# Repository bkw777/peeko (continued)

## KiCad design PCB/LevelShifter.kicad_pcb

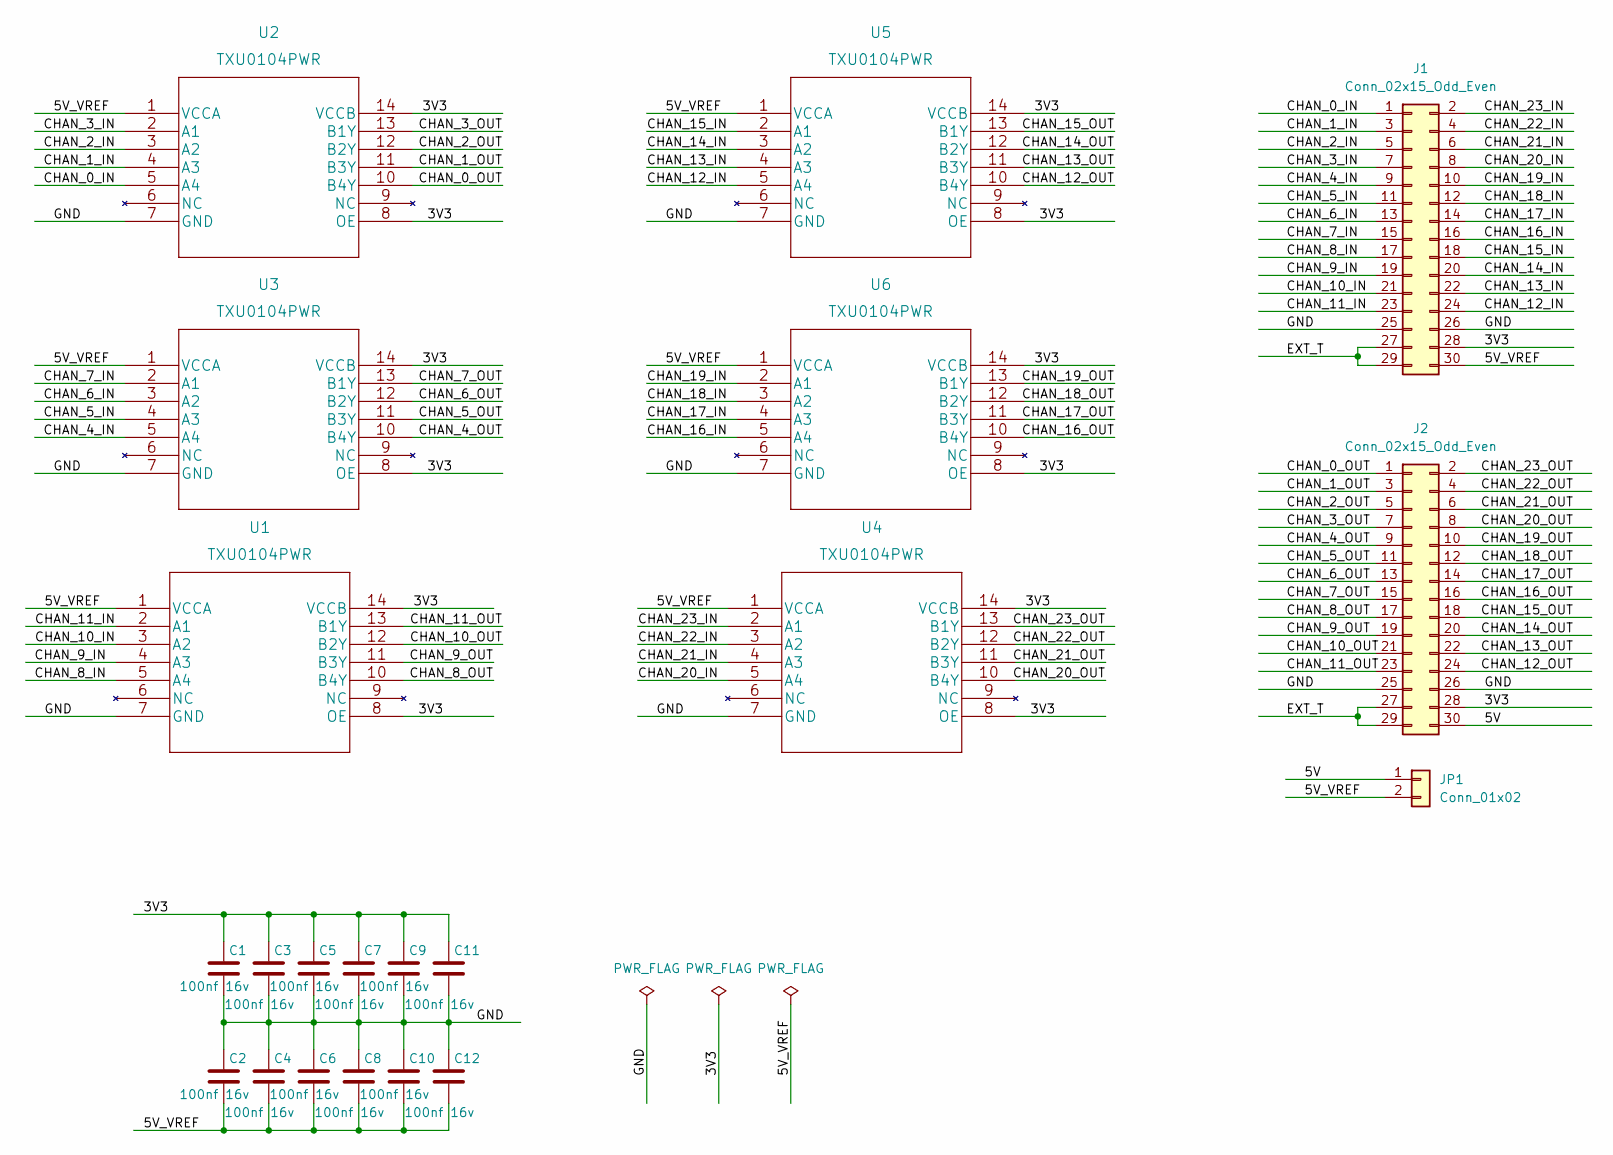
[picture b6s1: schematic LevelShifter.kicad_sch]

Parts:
C1, C2, C3, C4, C5, C6, C7, C8, C9, C10, C11, C12: 100nf 16v; C_0603_1608Metric
J1: Conn_02x15_Odd_Even; PinSocket_2x15_P2.54mm_Horizontal
J2: Conn_02x15_Odd_Even; PinHeader_2x15_P2.54mm_Horizontal
JP1: Conn_01x02; PinHeader_1x02_P2.54mm_Vertical
U1, U2, U3, U4, U5, U6: TXU0104PWR

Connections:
/3V3: C1.1, C3.1, C5.1, C7.1, C9.1, C11.1, J1.28, J2.28, U1.8 (OE), U1.14 (VCCB), U2.8 (OE), U2.14 (VCCB), U3.8 (OE), U3.14 (VCCB), U4.8 (OE), U4.14 (VCCB), U5.8 (OE), U5.14 (VCCB), U6.8 (OE), U6.14 (VCCB)
/5V: J2.30, JP1.1
/5V_VREF: C2.2, C4.2, C6.2, C8.2, C10.2, C12.2, J1.30, JP1.2, U1.1 (VCCA), U2.1 (VCCA), U3.1 (VCCA), U4.1 (VCCA), U5.1 (VCCA), U6.1 (VCCA)
/CHAN_0_IN: J1.1, U2.5 (A4)
/CHAN_0_OUT: J2.1, U2.10 (B4Y)
/CHAN_1_IN: J1.3, U2.4 (A3)
/CHAN_1_OUT: J2.3, U2.11 (B3Y)
/CHAN_2_IN: J1.5, U2.3 (A2)
/CHAN_2_OUT: J2.5, U2.12 (B2Y)
/CHAN_3_IN: J1.7, U2.2 (A1)
/CHAN_3_OUT: J2.7, U2.13 (B1Y)
/CHAN_4_IN: J1.9, U3.5 (A4)
/CHAN_4_OUT: J2.9, U3.10 (B4Y)
/CHAN_5_IN: J1.11, U3.4 (A3)
/CHAN_5_OUT: J2.11, U3.11 (B3Y)
/CHAN_6_IN: J1.13, U3.3 (A2)
/CHAN_6_OUT: J2.13, U3.12 (B2Y)
/CHAN_7_IN: J1.15, U3.2 (A1)
/CHAN_7_OUT: J2.15, U3.13 (B1Y)
/CHAN_8_IN: J1.17, U1.5 (A4)
/CHAN_8_OUT: J2.17, U1.10 (B4Y)
/CHAN_9_IN: J1.19, U1.4 (A3)
/CHAN_9_OUT: J2.19, U1.11 (B3Y)
/CHAN_10_IN: J1.21, U1.3 (A2)
/CHAN_10_OUT: J2.21, U1.12 (B2Y)
/CHAN_11_IN: J1.23, U1.2 (A1)
/CHAN_11_OUT: J2.23, U1.13 (B1Y)
/CHAN_12_IN: J1.24, U5.5 (A4)
/CHAN_12_OUT: J2.24, U5.10 (B4Y)
/CHAN_13_IN: J1.22, U5.4 (A3)
/CHAN_13_OUT: J2.22, U5.11 (B3Y)
/CHAN_14_IN: J1.20, U5.3 (A2)
/CHAN_14_OUT: J2.20, U5.12 (B2Y)
/CHAN_15_IN: J1.18, U5.2 (A1)
/CHAN_15_OUT: J2.18, U5.13 (B1Y)
/CHAN_16_IN: J1.16, U6.5 (A4)
/CHAN_16_OUT: J2.16, U6.10 (B4Y)
/CHAN_17_IN: J1.14, U6.4 (A3)
/CHAN_17_OUT: J2.14, U6.11 (B3Y)
/CHAN_18_IN: J1.12, U6.3 (A2)
/CHAN_18_OUT: J2.12, U6.12 (B2Y)
/CHAN_19_IN: J1.10, U6.2 (A1)
/CHAN_19_OUT: J2.10, U6.13 (B1Y)
/CHAN_20_IN: J1.8, U4.5 (A4)
/CHAN_20_OUT: J2.8, U4.10 (B4Y)
/CHAN_21_IN: J1.6, U4.4 (A3)
/CHAN_21_OUT: J2.6, U4.11 (B3Y)
/CHAN_22_IN: J1.4, U4.3 (A2)
/CHAN_22_OUT: J2.4, U4.12 (B2Y)
/CHAN_23_IN: J1.2, U4.2 (A1)
/CHAN_23_OUT: J2.2, U4.13 (B1Y)
/EXT_T: J1.27, J1.29, J2.27, J2.29
/GND: C1.2, C2.1, C3.2, C4.1, C5.2, C6.1, C7.2, C8.1, C9.2, C10.1, C11.2, C12.1, J1.25, J1.26, J2.25, J2.26, U1.7 (GND), U2.7 (GND), U3.7 (GND), U4.7 (GND), U5.7 (GND), U6.7 (GND)

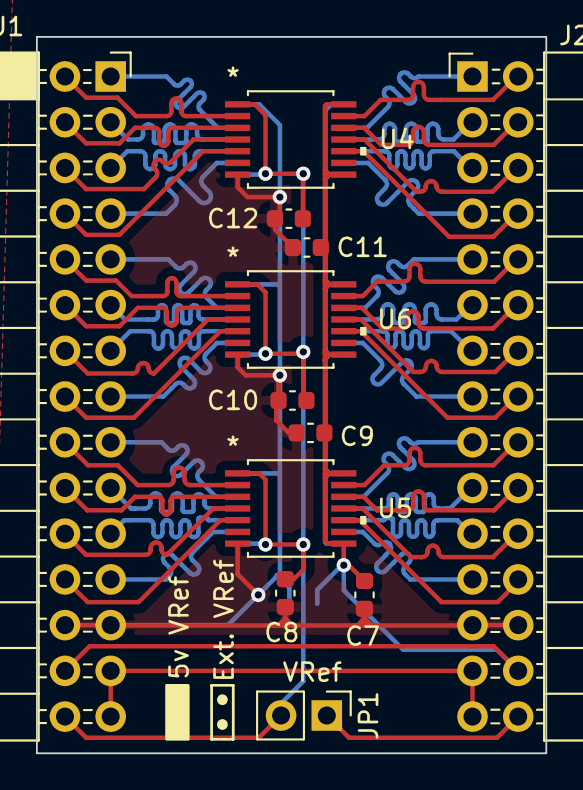
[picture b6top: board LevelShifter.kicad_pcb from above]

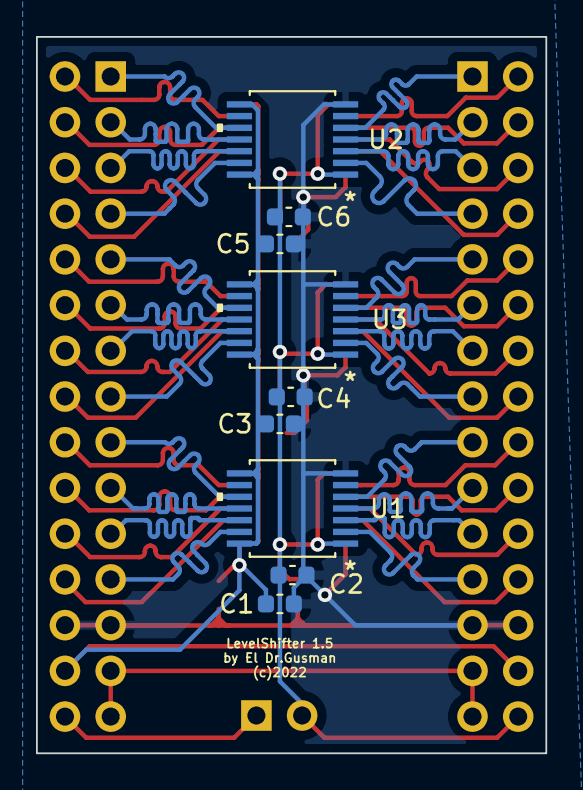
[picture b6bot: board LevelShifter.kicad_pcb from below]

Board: 2 copper layers, 28.3 x 39.8 mm, 21 parts (9 on the bottom side), 53 nets.

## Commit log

2024-09-19 redraw main & jasonyang boards
2024-09-19 indiscriminate gitignore
2024-09-20 level shifter
2024-09-20 pics
2024-09-20 shrink level shifter
2024-09-20 renumber level shifter
2024-09-20 junk pics
2024-09-21 annotation
2024-09-21 schematic for JY board, remove all but PCBs
2024-09-21 jy sch tidy
2024-09-21 jy pcb teardrops
2024-09-21 minor
2024-09-22 bom & readme
2024-09-23 fixup local symbols, footprints, models, move power traces inboard
2024-09-23 jy inner2 5v
2024-09-23 renders
2024-09-25 housing
2024-09-26 jy reduce from 4 layer to 2
2024-09-28 jy ground paths, jy housing
2024-09-30 peeko+
2024-09-30 local tssop14 footprint, redo short side traces on peeko+ & level shifter
2024-09-30 level shifter housing
2024-10-01 peeko+ housing render
2024-10-05 drop seperate level-shifter
2024-10-05 single scad model
2024-10-05 add fab bom and centroid exports
2024-10-06 switch to schottkys on brute
2024-10-06 local fiducial footprint
2024-10-07 make brute the same dimensions and port placement as regular peeko, use same housing for both
2024-10-07 make both boards have same chain pinout
2024-10-07 sch label
2024-10-07 pics, elecrow assembly bom
2024-10-07 refill zone
2024-10-08 CC BY-SA
2024-10-21 forgotten fillet track on brute
2024-12-05 silkscreen, readme, probe wires, enclosure wall behind pins
2024-12-30 boms
2025-02-11 shorten chain trace, delete duplicate footprints
2025-03-31 zigzag pi pico dip pins for friction fit
